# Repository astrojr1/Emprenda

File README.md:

# Emprenda
Effigy Labs Control Pedal control program - Free Open Source Software

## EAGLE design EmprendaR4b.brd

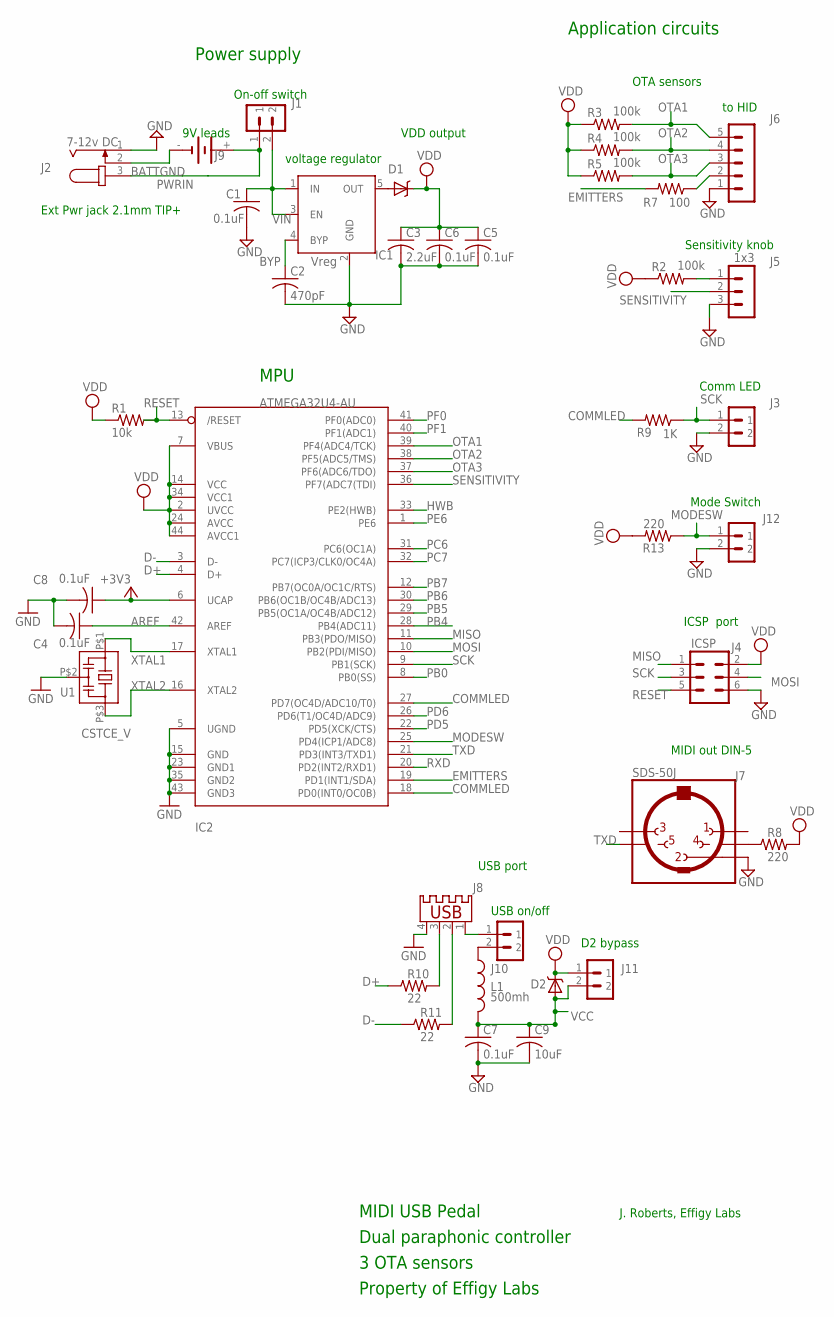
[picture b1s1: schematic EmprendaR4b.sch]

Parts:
C1: 0.1uF; C1206; MPN 0603YC104KAT2A
C2: 470pF; C0603; MPN C1608X7R1H471K
C3: 2.2uF; C1206
C4: 0.1uF; C0603; MPN 0603YC104KAT2A
C5, C6, C8: 0.1uF; C0603
C7: 0.1uF; C1206
C9: 10uF; C1206
D1, D2: DIODE-SCHOTTKY_; SMA-DIODE
IC1: Vreg; SOT23-5; MPN SPX5205M5-L-5-0
IC2: ATMEGA32U4-AU; TQFP44
J1, J10: SW1; MA02-1
J2: 7-12v DC; SPC4077; MPN SPC21364
J3, J12: LED; MA02-1
J4: ICSP; MA03-2; MPN 20021111-00006T4LF
J5: 1x3; MA03-1
J6: Pedal; MA05-1; MPN 05HR-6S-P-N
J7: SDS-50J
J8: B; 61729-0010BLF
J9: BATTERY-9V; 9V-BATTERY-SNAP
J11: USB-vdd; MA02-1
L1: 500mh; 0805
R1: 10k; R0805; MPN ERJ-3EKF1002V
R2, R3, R4, R5: 100k; R0805; MPN ERJ-6GEYJ104V
R7: 100; R0805; MPN ERJ-6GEYJ104V
R8, R13: 220; R0805; MPN ERJ-6GEYJ104V
R9: 1K; R0805; MPN ERJ-6GEYJ103V
R10, R11: 22; R0805
U1: CSTCE_V; MPN CSTCE16M0V53-R0

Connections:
+3V3: C8.1, IC2.6 (UCAP)
AREF: C4.1, IC2.42 (AREF)
BATTGND: J2.2, J9.-
BYP: C2.1, IC1.4 (BYP)
COMMLED: IC2.18 (PD0(INT0/OC0B)), IC2.27 (PD7(OC4D/ADC10/T0)), R9.2
D+: IC2.4 (D+), R10.1
D-: IC2.3 (D-), R11.1
EMITTERS: IC2.19 (PD1(INT1/SDA)), R7.2
EP: J6.2, R7.1
GND: C1.2, C2.2, C3.2, C4.2, C5.2, C6.2, C7.2, C8.2, C9.2, IC1.2 (GND), IC2.5 (UGND), IC2.15 (GND), IC2.23 (GND1), IC2.35 (GND2), IC2.43 (GND3), J2.1, J3.2, J4.6, J5.3, J6.1, J7.P$2 (2), J8.4, J12.2, U1.P$2 (2)
HWB: IC2.33 (PE2(HWB))
MIDIPWR: J7.P$4 (4), R8.1
MISO: IC2.11 (PB3(PDO/MISO)), J4.1
MODESW: IC2.25 (PD4(ICP1/ADC8)), J12.1, R13.1
MOSI: IC2.10 (PB2(PDI/MISO)), J4.4
unnamed: J8.1, J10.1
OTA1: IC2.39 (PF4(ADC4/TCK)), J6.5, R3.2
OTA2: IC2.38 (PF5(ADC5/TMS)), J6.4, R4.2
OTA3: IC2.37 (PF6(ADC6/TDO)), J6.3, R5.2
PB0: IC2.8 (PB0(SS))
PB4: IC2.28 (PB4(ADC11))
PB5: IC2.29 (PB5(OC1A/OC4B/ADC12))
PB6: IC2.30 (PB6(OC1B/OC4B/ADC13))
PB7: IC2.12 (PB7(OC0A/OC1C/RTS))
PC6: IC2.31 (PC6(OC1A))
PC7: IC2.32 (PC7(ICP3/CLK0/OC4A))
PD5: IC2.22 (PD5(XCK/CTS))
PD6: IC2.26 (PD6(T1/OC4D/ADC9))
PE6: IC2.1 (PE6)
PF0: IC2.41 (PF0(ADC0))
PF1: IC2.40 (PF1(ADC1))
PWRIN: J1.1, J2.3, J9.+
RESET: IC2.13 (/RESET), J4.5, R1.2
RVOUT: D1.A, IC1.5 (OUT)
RXD: IC2.20 (PD2(INT2/RXD1))
SCK: IC2.9 (PB1(SCK)), J3.1, J4.3, R9.1
SENSITIVITY: IC2.36 (PF7(ADC7(TDI)), J5.2
SENSPWR: J5.1, R2.2
TXD: IC2.21 (PD3(INT3/TXD1)), J7.P$5 (5)
USB_D+: J8.3, R10.2
USB_D-: J8.2, R11.2
VBUS: J10.2, L1.1
VCC: C7.1, C9.1, D2.A, J11.2, L1.2
VDD: C3.1, C5.1, C6.1, D1.C, D2.C, IC2.2 (UVCC), IC2.7 (VBUS), IC2.14 (VCC), IC2.24 (AVCC), IC2.34 (VCC1), IC2.44 (AVCC1), J4.2, J11.1, R1.1, R2.1, R3.1, R4.1, R5.1, R8.2, R13.2
VIN: C1.1, IC1.1 (IN), IC1.3 (EN), J1.2
XTAL1: IC2.17 (XTAL1), U1.P$1 (1)
XTAL2: IC2.16 (XTAL2), U1.P$3 (3)

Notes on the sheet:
J. Roberts, Effigy Labs
Property of Effigy Labs
MIDI USB Pedal
D2 bypass
Comm LED
ICSP port
Sensitivity knob
to HID
OTA sensors
MIDI out DIN-5
MPU
USB port
USB on/off
Power supply
Ext Pwr jack 2.1mm TIP+
9V leads
On-off switch
Mode Switch
Application circuits
VDD output
Dual paraphonic controller
3 OTA sensors
voltage regulator

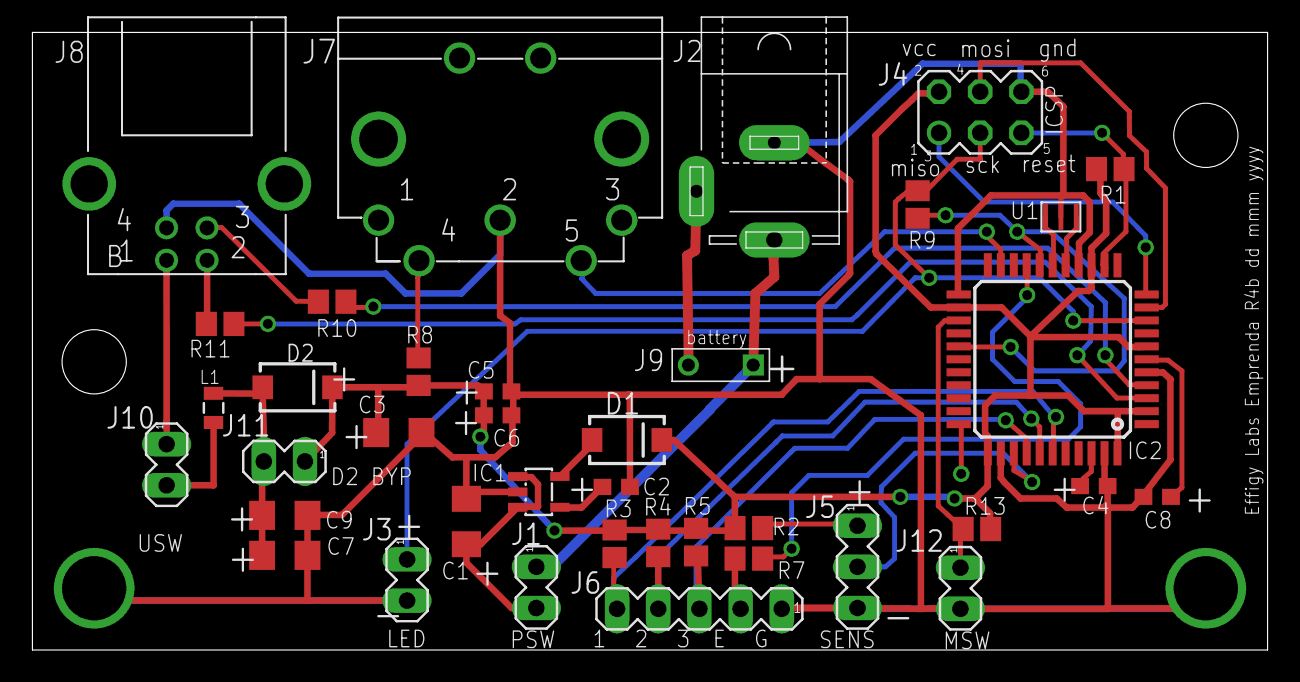
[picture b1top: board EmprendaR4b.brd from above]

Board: 2 copper layers, 76.2 x 38.1 mm, 38 parts (0 on the bottom side), 33 nets.

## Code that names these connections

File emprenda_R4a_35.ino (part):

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   A0 = OTA1
   so the pin mappings will not work interchangeably.

   dummy pin - to avoid cross-talk influence between the last OTA read and the sensitivity knob.
   
  TO-DO:
    - program rewrite
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const static int WORKINGRANGE_COL = 7;     // set of messageable values
const static int SWITCH_COL = 8;           // if true, OTA operates on on-off only
const static int MIDI_CMD_COL = 9;         // the function assigned to this ota
const static int SENSITIVITY_COL = 10;     // current sensitivity of this ota
const static int ACTIVE_COL = 11;          // current sensitivity of this ota
//const static int WHATEVER_COL = 12;          // another column of OTA values

/* left-right locking:
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int middle_ota = 2;

// pin maps.  the An statics map to the pin numbers on the teensy 2.0
int OTA1 = A0;  //left/down
int OTA2 = A1;  //right/up
int OTA3 = A2;  //middle/effect
int sensorPin = OTA1;            // set to either the left or right sensor by the locker in LR mode - default = left or OTA1

const int numberOfSamples = 2000; // number of calibration samples to average, 
// currently at 2000 samples, approximately 1 second of clock time.  this is bypassed during mode switch, currently calibration only happens at setup.
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int sensorPinActive = 0;    // which pedal is active; 1 = down, 2 = up, 0 = neither

// LED outputs
int pedalLedPin = 2;      // emitters
int commLedPin = 3;      // comm LED
int fadeLedPin = 6;      // fade LED, adds base current at variable brightness via pwm to let the comm led phase in an adjustable range off of black at the bottom
// allow analogwrite
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int8_t hbdelta = 8;
int fadeSpeedMax = 40;
int fadeSpeedMin = 8;
int fadespeed = 40; // vary from 10 to 100 - when centered, cycle according to sensitivity.  when pedal is operating, vary according to OTA position.
// 40 turns out to be the max not 80 as was before
unsigned long cyclestart; // led fader timer
/*
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int ledFadeBrightness = 200; // default value: start "on"    ******** fix this and other parts of this for proper phasing

// sensitivity knob input
int sensitivityKnobPin = A3;          // sensitivity knob input pin # for #33+ on atmega32u4 compiling as a teeonardu

int dummypin = A4;                    // unused pin.  read before reading the knob value.  this is necessary to discharge the hold/sample capacitor in the chip to get an 
                                      // accurate reading.  If this is not done, the knob value will be influenced by the last value read from the last OTA.  In this case, 
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int sensitivityKnobValue = 255;       // default value = half-way
int sensitivityKnobMaxValue = 510;    // #34's maximum knob reading

int knobjitter = 4;                   // variance of sensitivity knob - to 4 for #34 12/24/16

//int knobjitter = 3;                   // variance of sensitivity knob - pped from 3 to 10 for #32
//int knobjitter = 3;                   // variance of sensitivity knob - pped from 3 to 10 for #32
                                      // set to 6 for #33 - sep 1 2016 - 3 expressed jitter in the middle of the range
                                      // set back to 3 for #34 after fixing the knob cross-talk issue between ota3 and the knob reading - idles nice and tight now

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// map sensitivity knob max to 0 on this working range.
// sensitivity knob changes decrease under but never increase over this number

//int knobsensitivity = 2;              // sensitivity knob sensitivity dejitter factor
int sensitivity = 4;              // pedal sensitivity dejitter factor - nice and low for better/later pedals
                                      // this changes dynamically, the initial value is not used
                                      // setting to 4 just coz for #34
                                      
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  pinMode(fadeLedPin, OUTPUT);
  //digitalWrite(fadeLedPin, HIGH);  // turn on comm LED
  digitalWrite(commLedPin, HIGH);  // turn on comm LED
  digitalWrite(pedalLedPin, HIGH);  // turn on emitters

  // maybe don't need ********
  blinkCommLED(setupblinkinterval, 2); // indicate to user and give pedal sensors time to stabilize under illumination
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  }

  // read the knob value
  sensitivityKnobValue = analogRead(dummypin); // read something besides OTA3 to decouple the hold/sample capcitor's influence on the OTA3 and the knob.
  sensitivityKnobValue = analogRead(sensitivityKnobPin);

  //sensitivityKnobValue = min(sensitivityKnobMinValu4e, sensitivityKnobValue);
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
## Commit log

2017-03-06 corrected text and layout
2017-03-06 corrected layout and text

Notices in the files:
emprenda_R4a_35.ino:
(C)2012-2017, Effigy Labs
PUBLISHED AS FREE OPEN SOURCE SOFTWARE (FOSS) - see LICENSE.TXT
parts and their libraries:
SparkFun-Passives: Licensing: CC v3.0 Share-Alike You are welcome to use this library for commercial purposes.
